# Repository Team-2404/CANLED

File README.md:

# CANLED
*An open source CAN LED controller for FRC*

> [!NOTE]
> Picture TBD

## Overview

CANLED is an open source LED controller by FRC team 2404 which communicates over the 
CAN protocol. Based on the ATmega328P microcontroller and MCP2515/2561 CAN 
controller/transciever, this project repository includes the parts (`hardware/docs/`),
schematics (`hardware/kicad/`), firmware (`firmware/canled/`), and software (`software/`) 
needed to assemble the controller and use it with wpilib for FRC. By default set up to control LED strips using the WS2812B controller.

An AVR programmer is needed to flash the firmware using the Arduino IDE.

## Flashing firmware

These instructions assume you are using Windows and a generic USBasp AVR programmer such as [this](https://www.amazon.com/HiLetgo-ATMEGA8-Programmer-USBasp-Cable/dp/B00AX4WQ00?dib=eyJ2IjoiMSJ9.Vpd_TJZkp3x6e6H-i_2vonEUFtTd_0-I6H72u0k_G6s_0to9lSws388s62Q9_aR6_DBn9vL4UkvdUUsjs0d44WYar1vorjVRZY5iNrlMiofNUsc24RplOz-4FCIztb9BsEYEx1MmU4Cnw9Y-3BFWIDUoKXlg4rsoi04-QZFTduGaAsc8hNKOXMywyb7ADZe4hB5U-F0pv_-JWntyFR8pmCsvWxa0H9oXJf_dMJj0bhA.4N6-gxB3QFesddG2YDatRCVYgj06Y0Q0Sk0GaxjhOEg&dib_tag=se&keywords=avr+programmer&qid=1774985295&sr=8-5). 
First, [install zadig.exe](https://zadig.akeo.ie/). Plug in your programmer, connect the CANLED,
and open zadig. Find the USBasp device in the drop-down menu and select it. Choose the WinUSB driver
on the right side using the arrows and click install. Once the driver is installed, open Arduino IDE.
Open up the canled.ino file in the firmware directory (`firmware/canled`) and open up the "tools" 
drop-down menu. Select Arduino Uno as the board and USBasp as the programmer. Open up the "sketch" 
drop-down menu and select "install using programmer". If there is an error, try unplugging and 
replugging the programmer. 

## Contributors

- @ConorKellyGerakos
- @koshan-dawlaty
- @jakehlee (mentor)

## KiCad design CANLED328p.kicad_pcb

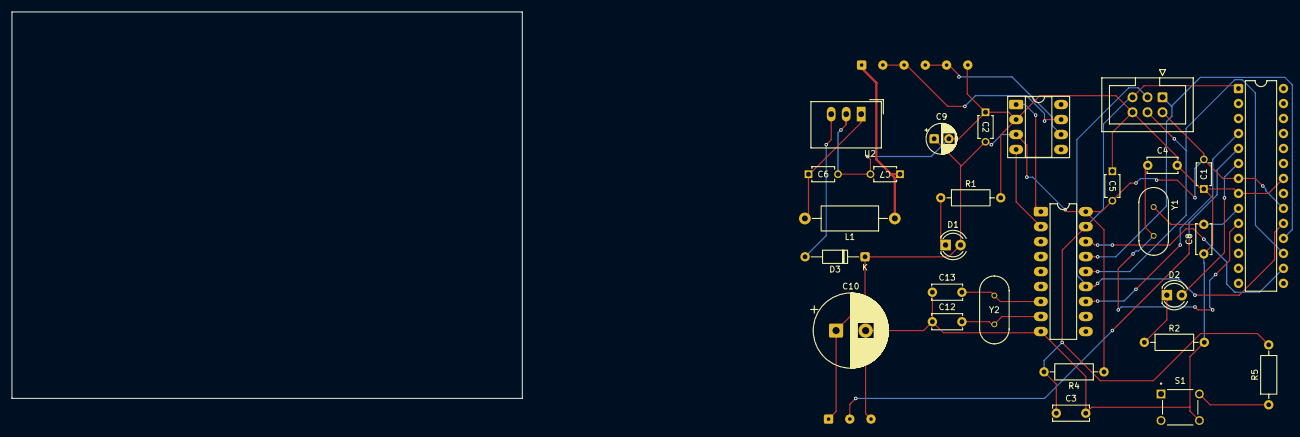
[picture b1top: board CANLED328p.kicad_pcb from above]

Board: 2 copper layers, 86.5 x 65.5 mm, 30 parts (0 on the bottom side), 24 nets.

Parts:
C1, C2, C5: 100 n; K104K10X7RF5UH5_VIS
C3: 0.1 u; C_Disc_D6.0mm_W2.5mm_P5.00mm
C4, C8, C12, C13: 22 p; C_Disc_D5.0mm_W2.5mm_P5.00mm
C6, C7: 1 u; K104K10X7RF5UH5_VIS
C9: 10 u; CP_Radial_D5.0mm_P2.50mm
C10: 1000 u; CP_Radial_D12.5mm_P5.00mm
D1: BLUE; LED_D4.0mm
D2: GREEN; LED_D4.0mm
D3: D; D_DO-35_SOD27_P10.16mm_Horizontal
J1: Conn_01x06_Socket; SolderWire-0.1sqmm_1x06_P3.6mm_D0.4mm_OD1mm
J2: Conn_01x03_Socket; SolderWire-0.1sqmm_1x03_P3.6mm_D0.4mm_OD1mm
J3: AVR-ISP-6; IDC-Header_2x03_P2.54mm_Vertical
L1: 5.6 uH; L_Axial_L9.5mm_D4.0mm_P15.24mm_Horizontal_Fastron_SMCC
R1, R2: 560; R_Axial_DIN0207_L6.3mm_D2.5mm_P10.16mm_Horizontal
R4: 10 K; R_Axial_DIN0207_L6.3mm_D2.5mm_P10.16mm_Horizontal
R5: 1 K; R_Axial_DIN0207_L6.3mm_D2.5mm_P10.16mm_Horizontal
S1: TS02-66-55-BK-100-LCR-D; SW_TS02-66-55-BK-100-LCR-D
U1: MCP2515-I_SO; DIP-18_W7.62mm_LongPads
U2: TSR_1-2450; Converter_DCDC_TRACO_TSR-1_THT
U3: MCP2561-E_SN; DIP-8_W7.62mm_Socket_LongPads
U4: ATmega328-P; DIP-28_W7.62mm
Y1: 16 MHz; XTAL_HC49P488W46L1150T500H350
Y2: 8 MHz; XTAL_HC49P488W46L1150T500H350

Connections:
+5V: C1.2, C2.2, C5.2, C9.1, C10.1, D1.2 (A), D3.1 (K), J2.1, J3.2 (VCC), R4.1, U1.18 (VDD), U3.3 (VDD), U4.7 (VCC), U4.20 (AVCC)
+12V: C7.1, J1.1, L1.1
CANHP: J1.2, J1.3, U3.7 (CANH)
CANLN: J1.4, J1.5, U3.6 (CANL)
DIO: J2.2, U4.5 (PD3)
GND: C1.1, C2.1, C3.2, C4.2, C5.1, C6.2, C7.2, C8.1, C9.2, C10.2, C12.1, C13.1, J1.6, J2.3, J3.6 (GND), R1.2, R2.2, S1.4, U1.9 (VSS), U2.2 (GND), U3.2 (VSS), U4.8 (GND), U4.22 (GND)
INT: U1.12 (~INT), U4.4 (PD2)
LED1: D2.2 (A), U4.6 (PD4)
MISO: J3.1 (MISO), U1.15 (SO), U4.18 (PB4)
MOSI: J3.4 (MOSI), U1.14 (SI), U4.17 (PB3)
unnamed: D1.1 (K), R1.1
unnamed: D2.1 (K), R2.1
unnamed: D3.2 (A), U2.3 (Vout)
unnamed: R5.1, S1.2
unnamed: C6.1, L1.2, U2.1 (Vin)
unnamed: C8.2, U4.9 (XTAL1/PB6), Y1.1
unnamed: C4.1, U4.10 (XTAL2/PB7), Y1.2
O1: C12.2, U1.8 (OSC1), Y2.1
O2: C13.2, U1.7 (OSC2), Y2.2
RST: C3.1, J3.5 (~RST), R4.2, R5.2, U1.17 (~RESET), U4.1 (~RESET/PC6)
RXCAN: U1.2 (RXCAN), U3.4 (RXD)
SCK: J3.3 (SCK), U1.13 (SCK), U4.19 (PB5)
SS: U1.16 (~CS), U4.16 (PB2)
TXCAN: U1.1 (TXCAN), U3.1 (TXD)

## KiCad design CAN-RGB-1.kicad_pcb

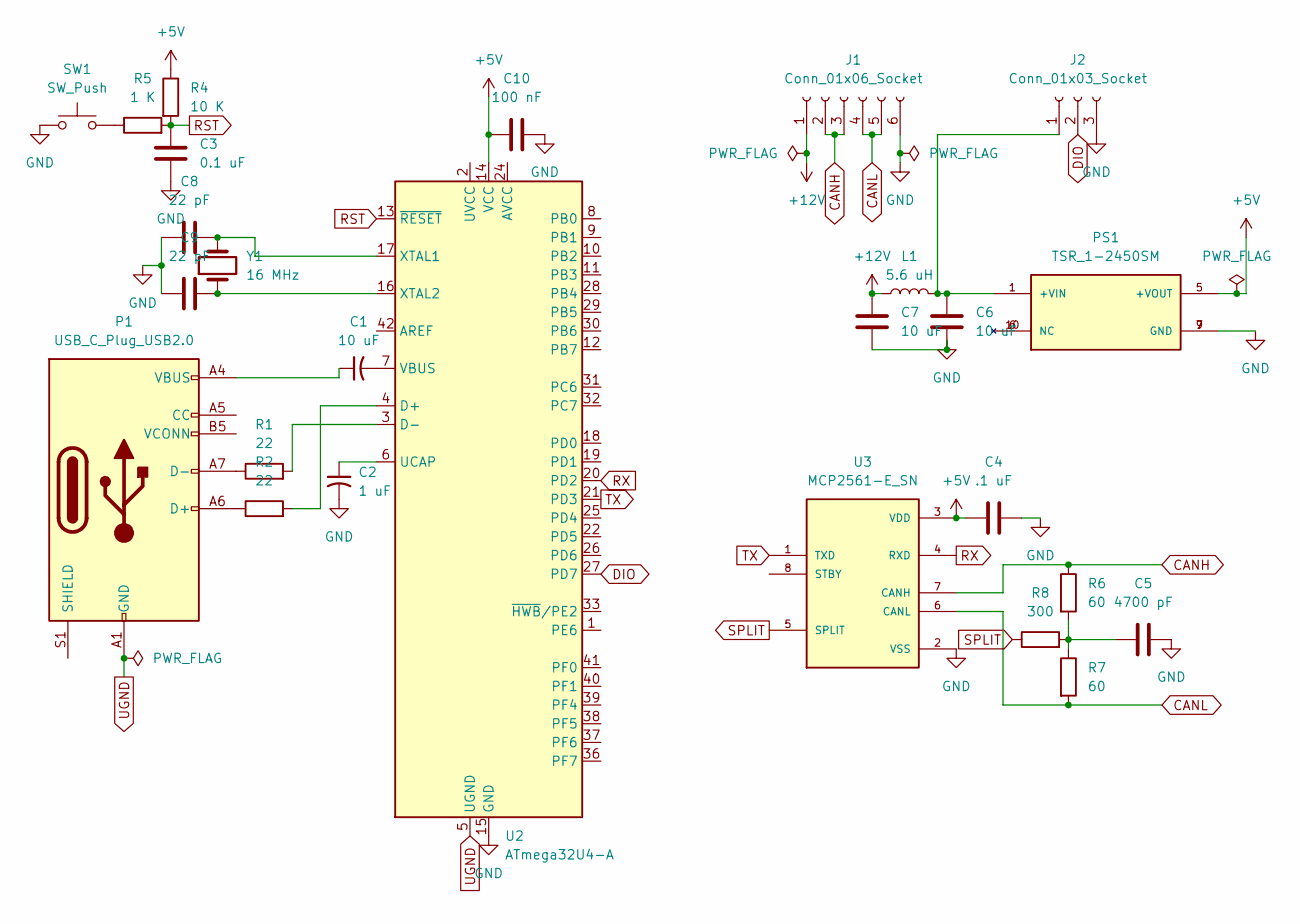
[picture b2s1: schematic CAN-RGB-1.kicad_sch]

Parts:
C1, C6, C7: 10 uF; C_0201_0603Metric
C2: 1 uF; C_0201_0603Metric
C3: 0.1 uF; C_0201_0603Metric
C4: .1 uF; C_0201_0603Metric
C5: 4700 pF; C_0201_0603Metric
C8, C9: 22 pF; C_0201_0603Metric
C10: 100 nF; C_0201_0603Metric
J1: Conn_01x06_Socket; SolderWire-0.1sqmm_1x06_P3.6mm_D0.4mm_OD1mm
J2: Conn_01x03_Socket; SolderWire-0.1sqmm_1x03_P3.6mm_D0.4mm_OD1mm
L1: 5.6 uH; L_0201_0603Metric
P1: USB_C_Plug_USB2.0; USB_C_Receptacle_HCTL_HC-TYPE-C-16P-01A
PS1: TSR_1-2450SM; CONV_TSR_1-2450SM; PARTREV May 26, 2020
R1, R2: 22; R_0402_1005Metric
R4: 10 K; R_0612_1632Metric
R5: 1 K; R_0201_0603Metric
R6, R7: 60; R_0201_0603Metric
R8: 300; R_0201_0603Metric
SW1: SW_Push; SW_SPST_CK_RS282G05A3
U2: ATmega32U4-A; TQFP-44_10x10mm_P0.8mm
U3: MCP2561-E_SN; SOIC127P600X175-8N; PARTREV C
Y1: 16 MHz; Crystal_HC49-U_Vertical

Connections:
+5V: C4.1, C10.1, PS1.5 (+VOUT), R4.1, U2.14 (VCC), U2.34 (VCC), U3.3 (VDD)
+12V: C7.1, J1.1, L1.1
CANH: J1.2, J1.3, R6.1, U3.7 (CANH)
CANL: J1.4, J1.5, R7.2, U3.6 (CANL)
DIO: J2.2, U2.27 (PD7)
GND: C2.2, C3.2, C4.2, C5.2, C6.2, C7.2, C8.1, C9.1, C10.2, J1.6, J2.3, PS1.7 (GND), PS1.9 (GND), SW1.1, U2.15 (GND), U2.23 (GND), U2.35 (GND), U2.43 (GND), U3.2 (VSS)
unnamed: C1.1, P1.A4 (VBUS), P1.A9 (VBUS), P1.B4 (VBUS), P1.B9 (VBUS)
unnamed: C5.1, R6.2, R7.1, R8.2
unnamed: C6.1, J2.1, L1.2, PS1.1 (+VIN)
unnamed: P1.A6 (D+), R2.1
unnamed: P1.A7 (D-), R1.1
unnamed: R5.1, SW1.2
unnamed: U2.24 (AVCC), U2.44 (AVCC)
unnamed: R2.2, U2.4 (D+)
unnamed: R1.2, U2.3 (D-)
unnamed: C2.1, U2.6 (UCAP)
unnamed: C1.2, U2.7 (VBUS)
unnamed: C8.2, U2.17 (XTAL1), Y1.2
unnamed: C9.2, U2.16 (XTAL2), Y1.1
RST: C3.1, R4.2, R5.2, U2.13 (~RESET)
RX: U2.20 (PD2), U3.4 (RXD)
SPLIT: R8.1, U3.5 (SPLIT)
TX: U2.21 (PD3), U3.1 (TXD)
UGND: P1.A1 (GND), P1.A12 (GND), P1.B1 (GND), P1.B12 (GND), U2.5 (UGND)

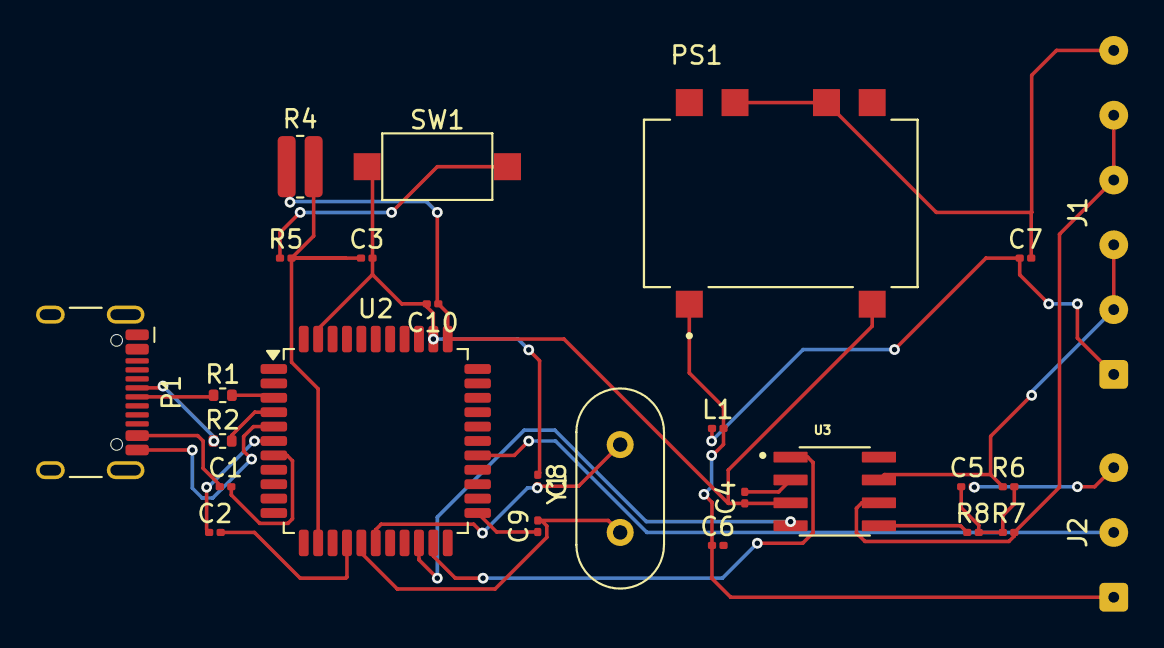
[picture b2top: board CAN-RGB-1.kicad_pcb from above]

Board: 2 copper layers, 26 parts (0 on the bottom side), 24 nets.

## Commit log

2025-05-12 previous work added
2025-05-13 reset and labels added
2025-06-08 schematic almost finished. 2551->61,pins and power supply
2025-06-11 more footprints added, schematic needs review
2025-06-13 Beginnings of PCB layout, needs to be reviewed, organized, and finalized.
2025-06-26 Layout connections mostly complete
2025-07-16 Early code added for testing
2025-08-25 all work from past month, board rev1
2025-09-03 rev1 with some fixes
2025-09-24 Beginning of rev1 redesign - major error fixed
2025-09-25 schematic cleaned up, new footprints req
2025-11-11 Arduino code added
2025-11-11 Update canled.ino w/ reminder
2025-12-04 temp library files for review
2025-12-09 New arduino code
2025-12-09 Issue fixed w/ py lib
2025-12-11 arduino code finalized for release, colors fixed
2025-12-13 old files removed
2025-12-13 files fully sorted
2025-12-13 added BOM for digikey
2025-12-16 Java lib tested, works w/ command based
2025-12-16 CANLED class new methods and docstrings
2025-12-30 Replaced BOM with simplified CSV This file is visible from GitHub and works with Digikey's Upload a List feature.
2025-12-30 Reorganization and firmware refactor
2025-12-30 Minor bugfixes and refactor. Commented out placeholder (?) python funcs
2025-12-30 Added Kicad plots of board
2025-12-31 lowercase dir
2025-12-31 update authorship
2025-12-31 Revise CANLED project overview in README
    Updated project description for clarity and correctness.
2026-01-05 code improved, javadocs added
2026-02-01 Now disables with robot, various changes-UNTESTED
2026-03-07 Library added, files updated to use library
2026-03-31 can now have LEDs automatically set to alliance color
2026-03-31 firmware instructions added
2026-04-01 code improved, alliance/disable don't work
